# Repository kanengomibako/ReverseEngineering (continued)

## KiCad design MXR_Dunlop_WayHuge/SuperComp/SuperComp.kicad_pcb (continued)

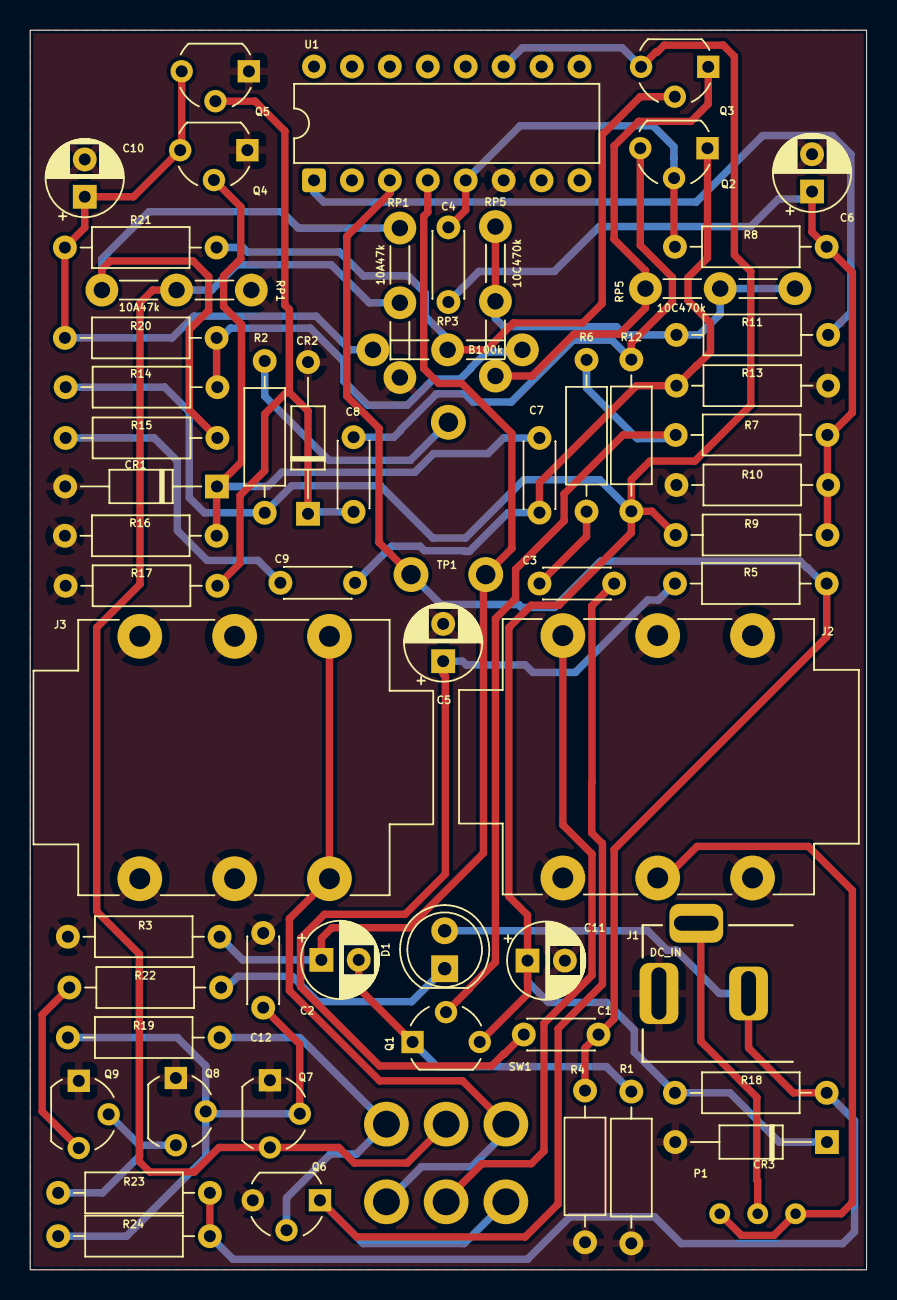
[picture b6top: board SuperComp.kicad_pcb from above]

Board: 2 copper layers, 56.0 x 83.0 mm, 61 parts (0 on the bottom side), 35 nets.

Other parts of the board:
RP1#2: 10A47k; my_pot_5mm
RP5#2: 10C470k; my_pot_5mm

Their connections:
GND: RP1#2.1; also elsewhere on the board
unnamed 17: RP5#2.3; also elsewhere on the board
unnamed 23: RP5#2.1, RP5#2.2; also elsewhere on the board
unnamed 26: RP1#2.3; also elsewhere on the board
Q7: RP1#2.2; also elsewhere on the board

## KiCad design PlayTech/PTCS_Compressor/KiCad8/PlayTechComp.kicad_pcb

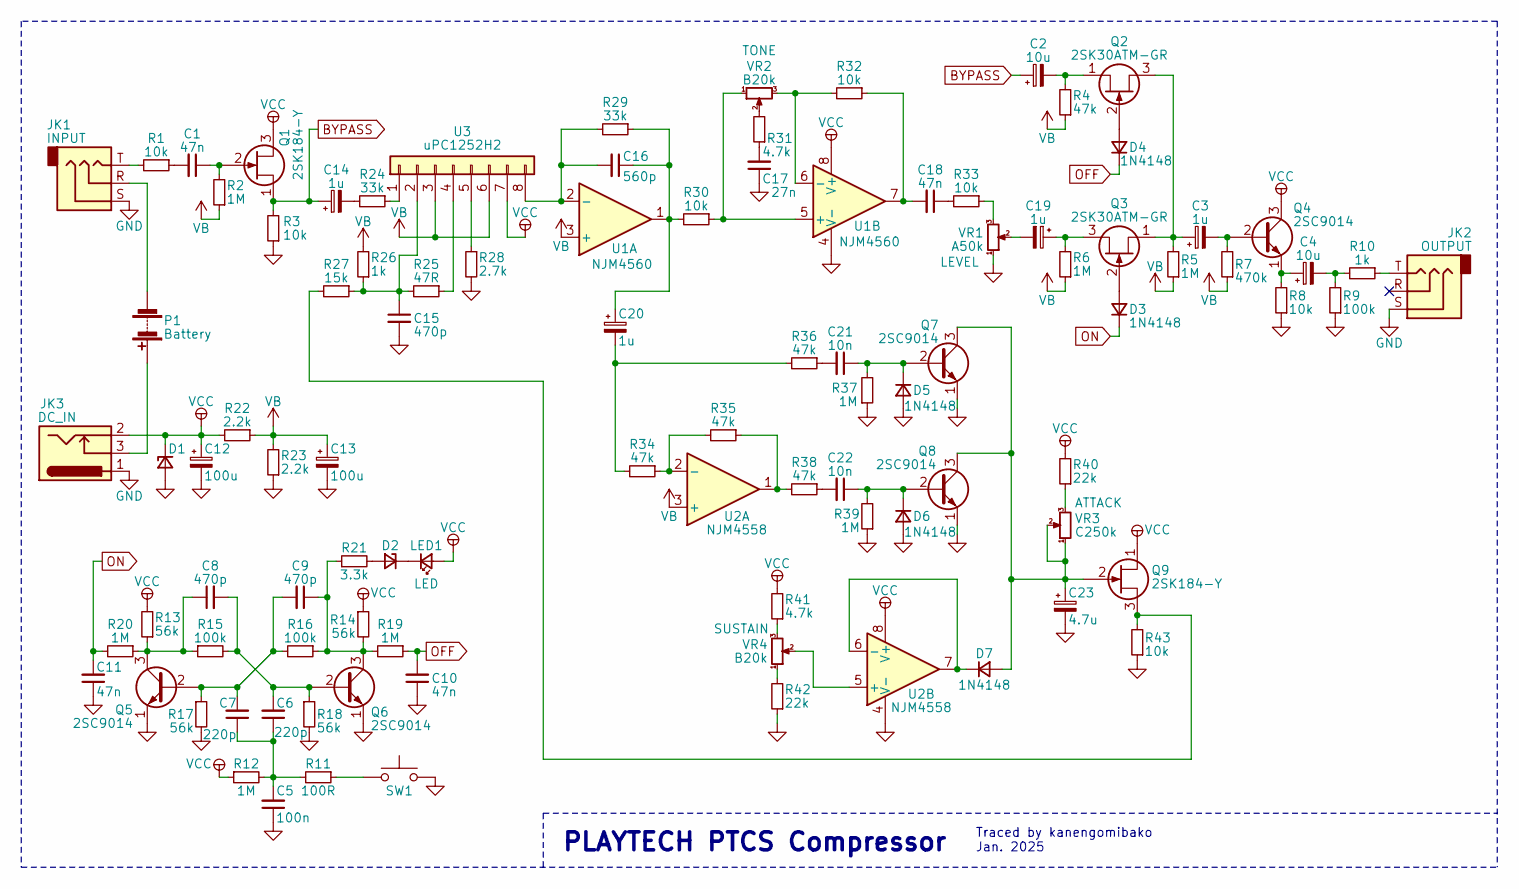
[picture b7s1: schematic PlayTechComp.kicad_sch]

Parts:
C1, C10, C11, C18: 47n; C_Disc_D4.3mm_W1.9mm_P5.00mm
C2, C4: 10u; CP_Radial_D5.0mm_P2.50mm
C3, C14, C19, C20: 1u; CP_Radial_D5.0mm_P2.50mm
C5: 100n; C_Disc_D4.3mm_W1.9mm_P5.00mm
C6, C7: 220p; C_Disc_D4.3mm_W1.9mm_P5.00mm
C8, C9, C15: 470p; C_Disc_D4.3mm_W1.9mm_P5.00mm
C12, C13: 100u; CP_Radial_D5.0mm_P2.50mm
C16: 560p; C_Disc_D4.3mm_W1.9mm_P5.00mm
C17: 27n; C_Disc_D4.3mm_W1.9mm_P5.00mm
C21, C22: 10n; C_Disc_D4.3mm_W1.9mm_P5.00mm
C23: 4.7u; CP_Radial_D5.0mm_P2.50mm
D1, D2: ?; D_DO-34_SOD68_P7.62mm_Horizontal
D3, D4, D5, D6, D7: 1N4148; D_DO-34_SOD68_P7.62mm_Horizontal
JK1: INPUT; PJ-603A
JK2: OUTPUT; PJ-603A
JK3: DC_IN; my_DC_Jack
LED1: LED; my_LED_5mm
P1: Battery; my_conn
Q1, Q9: 2SK184-Y; TO-92L_Inline_Wide
Q2, Q3: 2SK30ATM-GR; TO-92L_Inline_Wide
Q4, Q5, Q6, Q7, Q8: 2SC9014; TO-92L_Inline_Wide
R1, R3, R8, R30, R32, R33, R43: 10k; R_Axial_DIN0204_L3.6mm_D1.6mm_P7.62mm_Horizontal
R2, R5, R6, R12, R19, R20, R37, R39: 1M; R_Axial_DIN0204_L3.6mm_D1.6mm_P7.62mm_Horizontal
R4, R34, R35, R36, R38: 47k; R_Axial_DIN0204_L3.6mm_D1.6mm_P7.62mm_Horizontal
R7: 470k; R_Axial_DIN0204_L3.6mm_D1.6mm_P7.62mm_Horizontal
R9, R15, R16: 100k; R_Axial_DIN0204_L3.6mm_D1.6mm_P7.62mm_Horizontal
R10, R26: 1k; R_Axial_DIN0204_L3.6mm_D1.6mm_P7.62mm_Horizontal
R11: 100R; R_Axial_DIN0204_L3.6mm_D1.6mm_P7.62mm_Horizontal
R13, R14, R17, R18: 56k; R_Axial_DIN0204_L3.6mm_D1.6mm_P7.62mm_Horizontal
R21: 3.3k; R_Axial_DIN0204_L3.6mm_D1.6mm_P7.62mm_Horizontal
R22, R23: 2.2k; R_Axial_DIN0204_L3.6mm_D1.6mm_P7.62mm_Horizontal
R24, R29: 33k; R_Axial_DIN0204_L3.6mm_D1.6mm_P7.62mm_Horizontal
R25: 47R; R_Axial_DIN0204_L3.6mm_D1.6mm_P7.62mm_Horizontal
R27: 15k; R_Axial_DIN0204_L3.6mm_D1.6mm_P7.62mm_Horizontal
R28: 2.7k; R_Axial_DIN0204_L3.6mm_D1.6mm_P7.62mm_Horizontal
R31, R41: 4.7k; R_Axial_DIN0204_L3.6mm_D1.6mm_P7.62mm_Horizontal
R40, R42: 22k; R_Axial_DIN0204_L3.6mm_D1.6mm_P7.62mm_Horizontal
SW1: SW; SW_PUSH-12mm
U1: NJM4560; DIP-8_W7.62mm
U2: NJM4558; DIP-8_W7.62mm
U3: uPC1252H2; SIP-8_19x3mm_P2.54mm
VR1: A50k; PinHeader_1x03_P2.54mm_Vertical
VR2, VR4: B20k; PinHeader_1x03_P2.54mm_Vertical
VR3: C250k; PinHeader_1x03_P2.54mm_Vertical

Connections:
BYPASS: C2.1, C14.1, Q1.1 (D), R3.2
GND: C5.1, C10.1, C11.1, C12.2, C13.2, C15.2, C17.1, C23.2, D1.2 (A), D5.2 (A), D6.2 (A), JK1.S, JK2.S, JK3.1, Q5.1 (E), Q6.1 (E), Q7.1 (E), Q8.1 (E), R3.1, R8.1, R9.1, R17.2, R18.2, R23.1, R28.2, R37.1, R39.1, R42.1, R43.1, SW1.2, U1.4 (V-), U2.4 (V-), VR1.1
unnamed: C1.2, R1.1
unnamed: C4.2, R9.2, R10.2
unnamed: C5.2, C6.1, C7.1, R11.2, R12.2
unnamed: C14.2, R24.2
unnamed: C16.1, C20.1, R29.1, R30.2, U1.1
unnamed: C17.2, R31.1
unnamed: C18.1, R33.2
unnamed: C18.2, R32.1, U1.7
unnamed: C19.2, VR1.2
unnamed: C20.2, R34.2, R36.2
unnamed: C21.2, R36.1
unnamed: C22.2, R38.1
unnamed: D2.2 (A), R21.2
unnamed: D2.1 (K), LED1.1 (K)
unnamed: D3.2 (A), Q3.2 (G)
unnamed: D4.2 (A), Q2.2 (G)
unnamed: C21.1, D5.1 (K), Q7.2 (B), R37.2
unnamed: C22.1, D6.1 (K), Q8.2 (B), R39.2
unnamed: C23.1, D7.2 (A), Q7.3 (C), Q8.3 (C), Q9.2 (G), VR3.1, VR3.2
unnamed: D7.1 (K), U2.6 (-), U2.7
unnamed: JK1.T, R1.2
unnamed: JK2.T, R10.1
unnamed: JK3.3, P1.1 (+)
unnamed: JK1.R, P1.2 (-)
unnamed: C1.1, Q1.2 (G), R2.2
unnamed: C3.1, Q2.3 (D), Q3.1 (S), R5.2
unnamed: C2.2, Q2.1 (S), R4.2
unnamed: C19.1, Q3.3 (D), R6.2
unnamed: C3.2, Q4.2 (B), R7.2
unnamed: C4.1, Q4.1 (E), R8.2
unnamed: C7.2, C9.2, Q5.2 (B), R16.2, R17.1
unnamed: C8.1, Q5.3 (C), R13.1, R15.1, R20.1
unnamed: C6.2, C8.2, Q6.2 (B), R15.2, R18.1
unnamed: C9.1, Q6.3 (C), R14.2, R16.1, R19.2, R21.1
unnamed: Q9.3 (S), R27.2, R43.2
unnamed: R11.1, SW1.1
unnamed: R31.2, VR2.2
unnamed: R33.1, VR1.3
unnamed: R35.1, R38.2, U2.1
unnamed: R40.1, VR3.3
unnamed: R41.1, VR4.3
unnamed: R42.2, VR4.1
unnamed: C16.2, R29.2, U1.2 (-), U3.8
unnamed: R30.1, U1.5 (+), VR2.1
unnamed: R32.2, U1.6 (-), VR2.3
unnamed: R34.1, R35.2, U2.2 (-)
unnamed: U2.5 (+), VR4.2
unnamed: R24.1, U3.1
unnamed: C15.1, R25.2, R26.1, R27.1, U3.2
unnamed: R25.1, U3.4
unnamed: R28.1, U3.5
OFF: C10.2, D4.1 (K), R19.1
ON: C11.2, D3.1 (K), R20.2
VB: C13.1, R2.1, R4.1, R5.1, R6.1, R7.1, R22.1, R23.2, R26.2, U1.3 (+), U2.3 (+), U3.3, U3.6
VCC: C12.1, D1.1 (K), JK3.2, LED1.2 (A), Q1.3 (S), Q4.3 (C), Q9.1 (D), R12.1, R13.2, R14.1, R22.2, R40.2, R41.2, U1.8 (V+), U2.8 (V+), U3.7

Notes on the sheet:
PLAYTECH PTCS Compressor
Traced by kanengomibako Jan. 2025

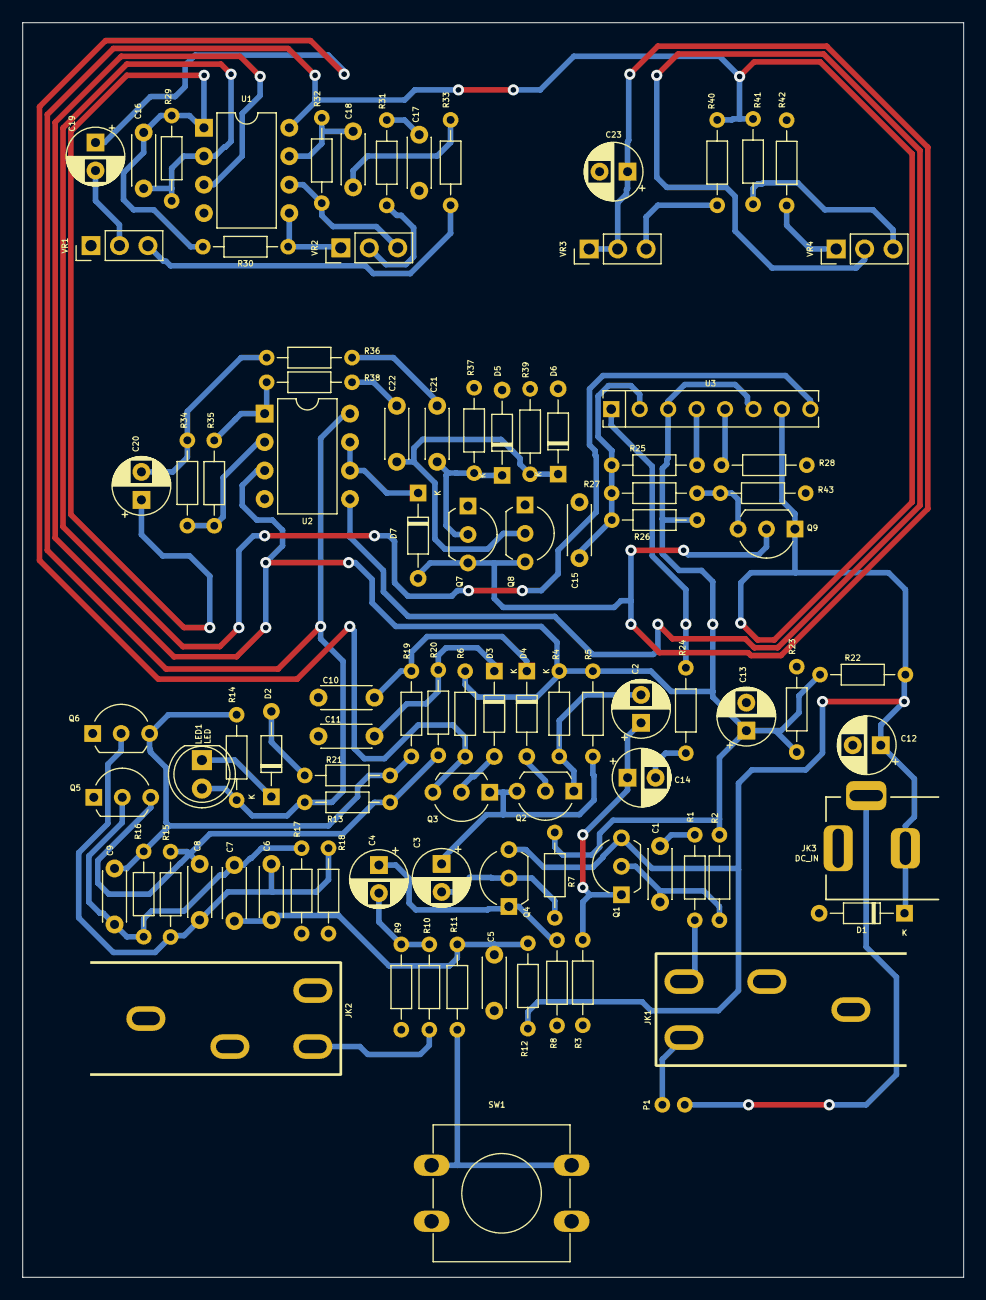
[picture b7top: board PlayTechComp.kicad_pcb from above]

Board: 2 copper layers, 84.0 x 112.0 mm, 95 parts (0 on the bottom side), 57 nets.

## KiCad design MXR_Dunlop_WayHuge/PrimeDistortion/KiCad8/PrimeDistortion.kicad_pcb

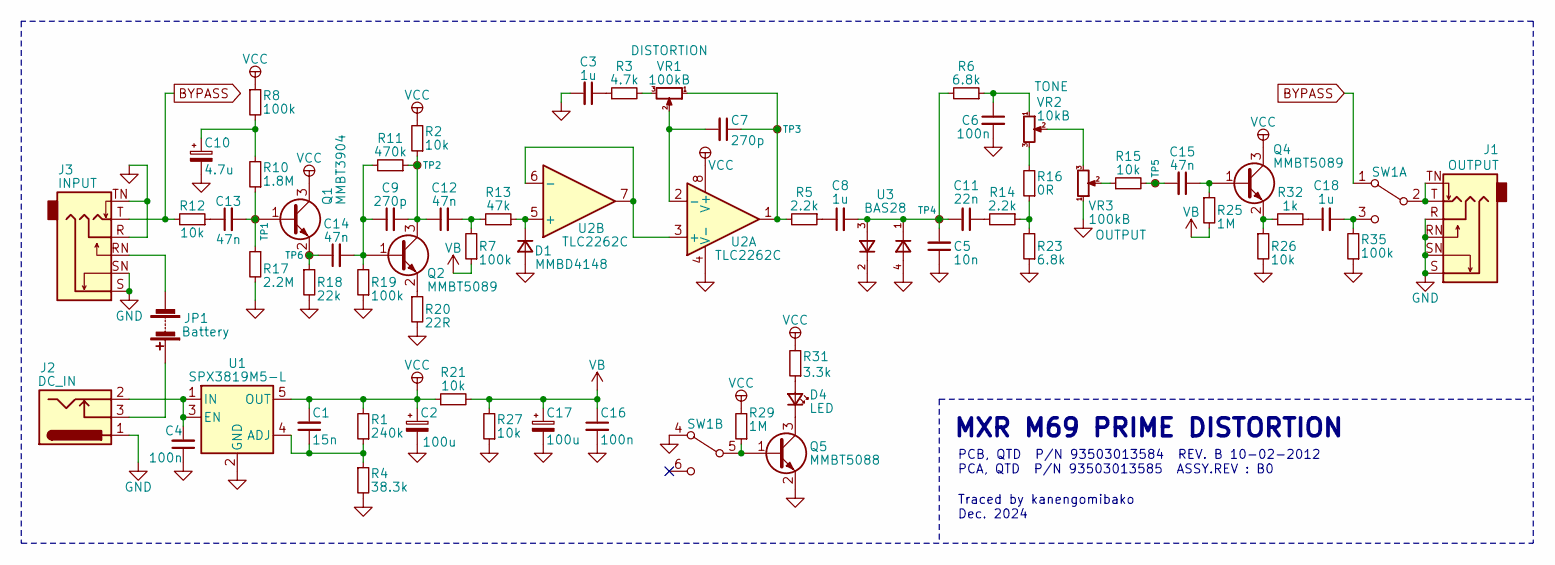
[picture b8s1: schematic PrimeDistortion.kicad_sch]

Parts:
C1: 15n; C_0805_2012Metric_Pad1.18x1.45mm_HandSolder
C2, C17: 100u; CP_Radial_D5.0mm_P2.50mm
C3, C8, C18: 1u; C_1206_3216Metric_Pad1.33x1.80mm_HandSolder
C4, C6, C16: 100n; C_0805_2012Metric_Pad1.18x1.45mm_HandSolder
C5: 10n; C_0805_2012Metric_Pad1.18x1.45mm_HandSolder
C7, C9: 270p; C_0805_2012Metric_Pad1.18x1.45mm_HandSolder
C10: 4.7u; CP_Radial_D5.0mm_P2.50mm
C11: 22n; C_1206_3216Metric_Pad1.33x1.80mm_HandSolder
C12, C13, C14, C15: 47n; C_1206_3216Metric_Pad1.33x1.80mm_HandSolder
D1: MMBD4148; SOT-23_mxr
D4: LED; LED_D3.0mm
J1: OUTPUT; Jack_6.35mm_Neutrik_NMJ6HCD2_Horizontal
J2: DC_IN; my_DC_Jack
J3: INPUT; Jack_6.35mm_Neutrik_NMJ6HCD2_Horizontal
JP1: Battery; my_conn
Q1: MMBT3904; SOT-23_mxr
Q2, Q4: MMBT5089; SOT-23_mxr
Q5: MMBT5088; SOT-23_mxr
R1: 240k; R_0805_2012Metric_Pad1.20x1.40mm_HandSolder
R2, R12, R15, R21, R26, R27: 10k; R_0805_2012Metric_Pad1.20x1.40mm_HandSolder
R3: 4.7k; R_0805_2012Metric_Pad1.20x1.40mm_HandSolder
R4: 38.3k; R_0805_2012Metric_Pad1.20x1.40mm_HandSolder
R5, R14: 2.2k; R_0805_2012Metric_Pad1.20x1.40mm_HandSolder
R6, R23: 6.8k; R_0805_2012Metric_Pad1.20x1.40mm_HandSolder
R7, R8, R19, R35: 100k; R_0805_2012Metric_Pad1.20x1.40mm_HandSolder
R10: 1.8M; R_0805_2012Metric_Pad1.20x1.40mm_HandSolder
R11: 470k; R_0805_2012Metric_Pad1.20x1.40mm_HandSolder
R13: 47k; R_0805_2012Metric_Pad1.20x1.40mm_HandSolder
R16: 0R; R_0805_2012Metric_Pad1.20x1.40mm_HandSolder
R17: 2.2M; R_0805_2012Metric_Pad1.20x1.40mm_HandSolder
R18: 22k; R_0805_2012Metric_Pad1.20x1.40mm_HandSolder
R20: 22R; R_0805_2012Metric_Pad1.20x1.40mm_HandSolder
R25, R29: 1M; R_0805_2012Metric_Pad1.20x1.40mm_HandSolder
R31: 3.3k; R_0805_2012Metric_Pad1.20x1.40mm_HandSolder
R32: 1k; R_0805_2012Metric_Pad1.20x1.40mm_HandSolder
SW1: SW2; PinHeader_2x03_P2.54mm_Vertical
TP1, TP2, TP3, TP4, TP5, TP6: -; my_SmallestPad_0-6mmDrill
U1: SPX3819M5-L; SOT-23-5
U2: TLC2262C; SO-8_3.9x4.9mm_P1.27mm
U3: BAS28; SOT-143
VR1, VR3: 100kB; my_pot_5mm
VR2: 10kB; my_pot_5mm

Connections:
BYPASS: J3.T, R12.2, SW1.1 (A)
GND: C2.2, C3.2, C4.1, C5.1, C6.2, C10.2, C16.2, C17.2, D1.1 (A), J1.R, J1.RN, J1.S, J1.SN, J2.1, J3.R, J3.S, J3.SN, J3.TN, Q5.2 (E), R4.2, R17.2, R18.2, R19.1, R20.2, R23.1, R26.2, R27.1, R35.1, SW1.4 (A), U1.2 (GND), U2.4 (V-), U3.2, U3.4 (2), VR3.1
unnamed: C3.1, R3.1
unnamed: C6.1, R6.1, VR2.1
unnamed: C7.1, R5.2, TP3.1, U2.1, VR1.1
unnamed: C8.1, R5.1
unnamed: C10.1, R8.2, R10.2
unnamed: C11.1, R14.2
unnamed: C5.2, C8.2, C11.2, R6.2, TP4.1, U3.1, U3.3
unnamed: C12.2, R7.2, R13.2
unnamed: C13.1, R12.1
unnamed: C15.2, R15.2, TP5.1
unnamed: C18.1, R32.2
unnamed: D1.3 (K), R13.1, U2.5 (+)
unnamed: D4.2 (A), R31.1
unnamed: D4.1 (K), Q5.3 (C)
unnamed: J2.3, JP1.1 (+)
unnamed: J3.RN, JP1.2 (-)
unnamed: C13.2, Q1.1 (B), R10.1, R17.1, TP1.1
unnamed: C14.1, Q1.2 (E), R18.1, TP6.1
unnamed: C9.1, C14.2, Q2.1 (B), R11.2, R19.2
unnamed: C9.2, C12.1, Q2.3 (C), R2.1, R11.1, TP2.1
unnamed: Q2.2 (E), R20.1
unnamed: C15.1, Q4.1 (B), R25.1
unnamed: Q4.2 (E), R26.1, R32.1
unnamed: Q5.1 (B), R29.1, SW1.5 (B)
unnamed: R3.2, VR1.3
unnamed: R14.1, R16.1, R23.2
unnamed: R15.1, VR3.2
unnamed: R16.2, VR2.3
unnamed: J1.T, J1.TN, SW1.2 (B)
unnamed: C18.2, R35.2, SW1.3 (C)
unnamed: C1.1, R1.1, R4.1, U1.4 (ADJ)
unnamed: C4.2, J2.2, U1.1 (IN), U1.3 (EN)
unnamed: U2.3 (+), U2.6 (-), U2.7
unnamed: C7.2, U2.2 (-), VR1.2
unnamed: VR2.2, VR3.3
VB: C16.1, C17.1, R7.1, R21.2, R25.2, R27.2
VCC: C1.2, C2.1, Q1.3 (C), Q4.3 (C), R1.2, R2.2, R8.1, R21.1, R29.2, R31.2, U1.5 (OUT), U2.8 (V+)

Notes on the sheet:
MXR M69 PRIME DISTORTION
Traced by kanengomibako Dec. 2024
PCB, QTD P/N 93503013584 REV. B 10-02-2012 PCA, QTD P/N 93503013585 ASSY.REV : B0

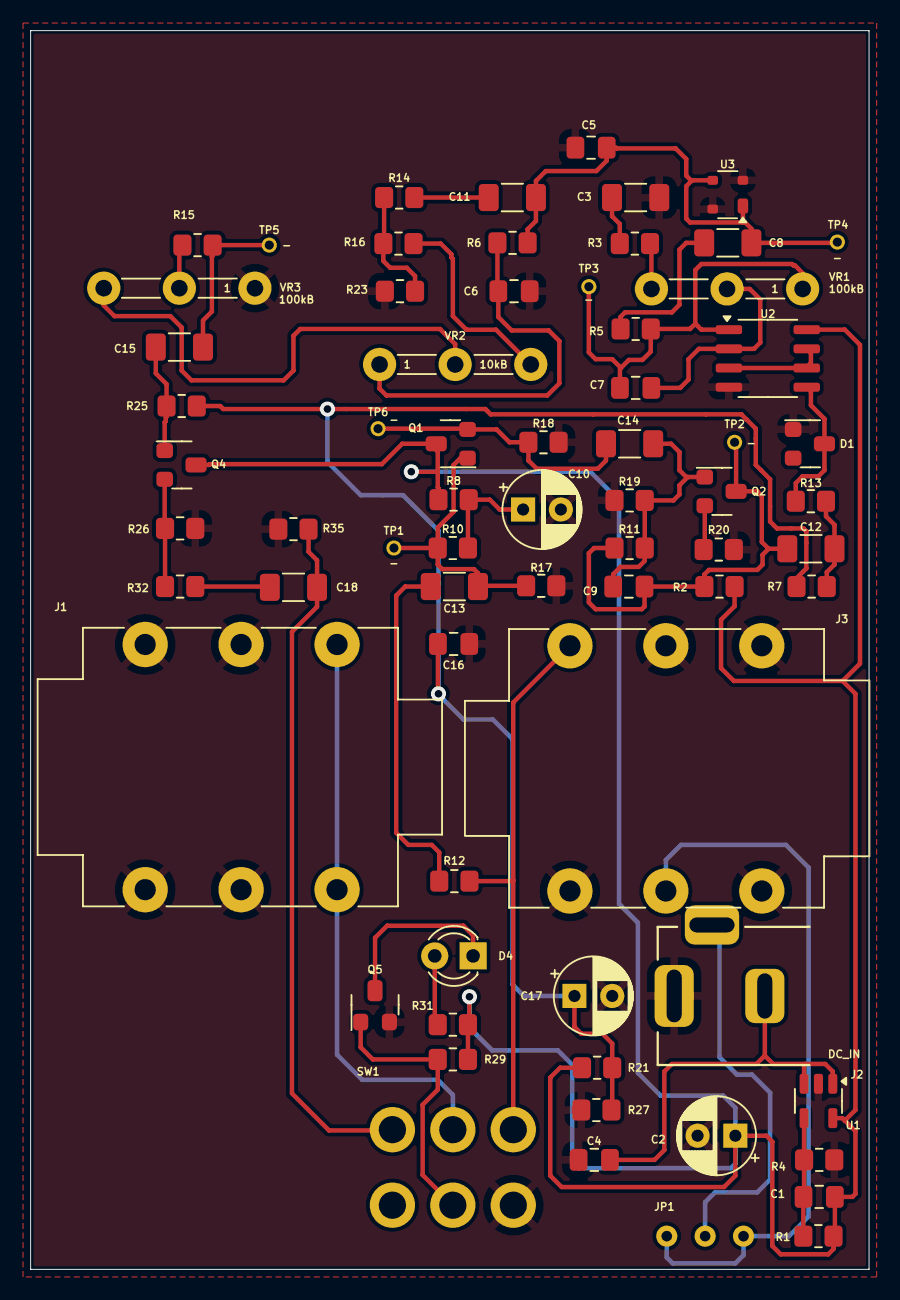
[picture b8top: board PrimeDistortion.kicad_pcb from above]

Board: 2 copper layers, 55.5 x 82.0 mm, 69 parts (0 on the bottom side), 39 nets.

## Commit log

2024-05-25 Reorganized folders
2024-06-01 Add Teisco Fuzz
2024-06-01 Add Cranetortoise HM-1
2024-09-26 Add PocketAmpMK2
2024-10-28 Add amPlug2ClassicRock
2024-10-28 Add LingonberryOverDrive
2024-11-25 Add SerotoninAddCBF
2024-12-23 Add RevivalDriveCompact
2025-01-24 Add PrimeDistortion
2025-01-24 Add PLAYTECH Compressor
2025-01-24 Add PLAYTECH 7 Band Equalizer
2025-05-03 Add Custom Comp
2025-05-16 Fix links
2025-05-16 Move RevivalDRIVE Compact Article
2025-07-07 Add Halcyon Green Overdrive
2025-09-06 Add Super Comp
2025-09-12 Add RAT2
2025-09-22 Add BRAT
2025-09-27 Add Caline CP-12 Pure Sky Overdrive schematic
2025-12-27 Add Distortion+
2026-01-01 Add POS DT-1
